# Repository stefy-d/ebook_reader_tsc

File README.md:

## **Manea Ștefania-Delia**
### **Grupa 335CC** 
<br><br>

# **Pașii de implementare**  
- Realizarea schematicului
- Plasarea componentelor pe PCB
- Trasarea circuitelor și optimizarea rutării semnalelor
- Încărcarea modelelor 3D pentru fiecare componentă
- Crearea bateriei și a display-ului
- Inserarea PCB-ului, a bateriei și a display-ului în carcasa 3D
<br><br> 

# **Diagramă bloc**
```` mermaid
graph TD;
    USB_C[USB C Connector & ESD Protection] -->|Power & Data| LDO[LDO Voltage Regulator];
    LDO -->|3.3V Power| ESP32[ESP32 C6];
    LDO -->|3.3V Power| SD[SD Card];
    LDO -->|3.3V Power| RTC[RTC Module DS3231SN];
    LDO -->|3.3V Power| Sensor[Environmental Sensor BME688];
    LDO -->|3.3V Power| Display[EPD Power];
    ESP32 -->|SPI| SD;
    ESP32 -->|I2C| RTC;
    ESP32 -->|I2C| Sensor;
    ESP32 -->|SPI| Display;
    ESP32 -->|GPIO| Button[Voltage Supervisor + Reset & Boot / IO Button];
    ESP32 -->|SPI| Flash[External NOR Flash 64MB];
    ESP32 -->|GPIO| ChargeLevel[Battery Charge Level];
    ESP32 -->|GPIO| Selector[Display Type Selector];
    ChargeController[Li-Po Battery Charging Controller] -->|Power| LDO;
    ChargeController -->|Battery Status| ChargeLevel;

`````
<br><br>

# **BOM (Bill Of Materials)**

| Componenta      | X      | Y      | Rotatie | Valoare | Package | Link | 
|----------------|--------|--------|----------|------------------------|----------------------------------------|-----------------------------------|  
| BOOT_BUTTON    | 23.90  | 108.41 | 180.00   | BUTTON_CUSYOMV1         | MYBUTTON | https://industry.panasonic.com/global/en/products/control/switch/light-touch/number/evqpuj02k |
| C1             | 154.64 | 6.13   | 90.00    | 100nF                  | ESP32_WROVER_EAGLE-LTSPICE_C0402       | https://componentsearchengine.com/part-view/CC0402MRX5R5BB106/YAGEO |
| C10            | 67.34  | 107.83 | 270.00   | 100nF                  | ESP32_WROVER_EAGLE-LTSPICE_C0402       | https://componentsearchengine.com/part-view/CC0402MRX5R5BB106/YAGEO |
| C10_SUPERCAP   | 93.09  | 55.34  | 90.00    | CPH3225A               | CAPCP3225X100N  | https://www.snapeda.com/parts/CPH3225A/Seiko+Instruments/view-part/?ref=eda |
| C1_BAT         | 107.73 | 50.25  | 0.00     | 4.7uF                  | ESP32_WROVER_EAGLE-LTSPICE_C0402       | https://componentsearchengine.com/part-view/CC0402MRX5R5BB106/YAGEO |
| C1_BAT1        | 109.19 | 37.99  | 0.00     | 4.7uF                  | ESP32_WROVER_EAGLE-LTSPICE_C0402       | https://componentsearchengine.com/part-view/CC0402MRX5R5BB106/YAGEO |
| C1_BAT2        | 104.58 | 40.47  | 90.00    | 4.7uF                  | ESP32_WROVER_EAGLE-LTSPICE_C0402       | https://componentsearchengine.com/part-view/CC0402MRX5R5BB106/YAGEO |
| C2             | 153.42 | 6.13   | 90.00    | 100nF                  | ESP32_WROVER_EAGLE-LTSPICE_C0402       | https://componentsearchengine.com/part-view/CC0402MRX5R5BB106/YAGEO |
| C2_BAT         | 120.94 | 51.25  | 90.00    | 4.7uF                  | ESP32_WROVER_EAGLE-LTSPICE_C0402       | https://componentsearchengine.com/part-view/CC0402MRX5R5BB106/YAGEO |
| C3             | 118.89 | 41.40  | 90.00    | 100uF                  | RCL_CT3528 | https://eu.mouser.com/ProductDetail/KYOCERA-AVX/F910J107MBAAJ6?qs=PqoDHHvF649LraCA%2FjeGXg%3D%3D |
| C4             | 90.95  | 35.19  | 90.00    | 4.7uF/25V              | ESP32_WROVER_EAGLE-LTSPICE_C0402       | https://componentsearchengine.com/part-view/CC0402MRX5R5BB106/YAGEO |
| C4_USB         | 149.29 | 50.17  | 90.00    | 100nF                  | ESP32_WROVER_EAGLE-LTSPICE_C0402       | https://componentsearchengine.com/part-view/CC0402MRX5R5BB106/YAGEO |
| C5             | 52.21  | 107.71 | 270.00   | 1uF                    | ESP32_WROVER_EAGLE-LTSPICE_C0402       | https://componentsearchengine.com/part-view/CC0402MRX5R5BB106/YAGEO |
| C5_USB         | 155.40 | 52.97  | 90.00    | 4.7uF                  | ESP32_WROVER_EAGLE-LTSPICE_C0402       | https://componentsearchengine.com/part-view/CC0402MRX5R5BB106/YAGEO |
| C6             | 27.30  | 107.83 | 270.00   | 100nF                  | ESP32_WROVER_EAGLE-LTSPICE_C0402       | https://componentsearchengine.com/part-view/CC0402MRX5R5BB106/YAGEO |
| C7             | 80.29  | 30.73  | 0.00     | 10uF                   | ESP32_WROVER_EAGLE-LTSPICE_C0402       | https://componentsearchengine.com/part-view/CC0402MRX5R5BB106/YAGEO |
| C8             | 84.28  | 52.43  | 180.00   | 100nF                  | ESP32_WROVER_EAGLE-LTSPICE_C0402       | https://componentsearchengine.com/part-view/CC0402MRX5R5BB106/YAGEO |
| C9             | 10.66  | 99.03  | 90.00    | 100nF                  | ESP32_WROVER_EAGLE-LTSPICE_C0402       | https://componentsearchengine.com/part-view/CC0402MRX5R5BB106/YAGEO |
| CHANGE_BUTTON  | 64.00  | 108.48 | 179.30   | BUTTON_CUSYOMV1         | MYBUTTON | https://industry.panasonic.com/global/en/products/control/switch/light-touch/number/evqpuj02k |
| CHG_LED        | 111.34 | 50.15  | 90.00    |                        | ADAFRUIT_CHIP-LED0603                  | https://www.snapeda.com/parts/KP-1608SURCK/Kingbright/view-part/?ref=search&t=LED%200603 |
| C_DELAY        | 51.93  | 101.29 | 269.50   | 100nF                  | ESP32_WROVER_EAGLE-LTSPICE_C0402       | https://componentsearchengine.com/part-view/CC0402MRX5R5BB106/YAGEO |
| D1             | 152.58 | 50.47  | 0.00     | USBLC6-2SC6Y            | SOT95P280X145-6N                       | https://www.snapeda.com/parts/USBLC6-2SC6Y/STMicroelectronics/view-part/?ref=eda |
| D10            | 44.62  | 38.77  | 90.00    | PGB1010603MR            | DIOC1608X36N                           | https://www.snapeda.com/parts/PGB1010603MR/Littelfuse/view-part/?ref=eda |
| D11            | 42.60  | 38.67  | 90.00    | PGB1010603MR            | DIOC1608X36N                           | https://www.snapeda.com/parts/PGB1010603MR/Littelfuse/view-part/?ref=eda |
| D12            | 38.38  | 38.87  | 90.00    | PGB1010603MR            | DIOC1608X36N                           | https://www.snapeda.com/parts/PGB1010603MR/Littelfuse/view-part/?ref=eda |
| D2             | 122.09 | 41.08  | 90.00    | ESP32_WROVER_AVX---SD0805S020S1R0_AVX_SD0805S020S1R0_0_0AVX_SD0805S020S1R0_0_0 | ESP32_WROVER_AVX---SD0805S020S1R0_AVX_SD0805S020S1R0_0 | https://eu.mouser.com/ProductDetail/KYOCERA-AVX/SD0805S020S1R0?qs=jCA%252BPfw4LHbpkAoSnwrdjw%3D%3D |
| D3             | 87.16  | 35.47  | 180.00   | MBR0530                 | SOD3716X135N                           | https://www.snapeda.com/parts/MBR0530/Onsemi/view-part/?ref=eda |
| D4             | 87.22  | 31.68  | 0.00     | MBR0530                 | SOD3716X135N                           | https://www.snapeda.com/parts/MBR0530/Onsemi/view-part/?ref=eda |
| D5             | 80.26  | 40.58  | 180.00   | MBR0530                 | SOD3716X135N                           | https://www.snapeda.com/parts/MBR0530/Onsemi/view-part/?ref=eda |
| D6             | 73.98  | 26.87  | 0.00     | PGB1010603MR            | DIOC1608X36N                           | https://www.snapeda.com/parts/PGB1010603MR/Littelfuse/view-part/?ref=eda |
| D7             | 83.64  | 68.93  | 0.00     | ESP32_WROVER_AVX---SD0805S020S1R0_AVX_SD0805S020S1R0_0_0AVX_SD0805S020S1R0_0_0 | ESP32_WROVER_AVX---SD0805S020S1R0_AVX_SD0805S020S1R0_0 | https://eu.mouser.com/ProductDetail/KYOCERA-AVX/SD0805S020S1R0?qs=jCA%252BPfw4LHbpkAoSnwrdjw%3D%3D |
| D8             | 14.96  | 98.57  | 0.00     | PGB1010603MR            | DIOC1608X36N                           | https://www.snapeda.com/parts/PGB1010603MR/Littelfuse/view-part/?ref=eda
| D9             | 33.14  | 47.17  | 270.00   | PGB1010603MR            | DIOC1608X36N                           | https://www.snapeda.com/parts/PGB1010603MR/Littelfuse/view-part/?ref=eda |
| EPD_C1         | 88.71  | 21.47  | 90.00    | 1uF/50V                | ESP32_WROVER_EAGLE-LTSPICE_C0402       | https://componentsearchengine.com/part-view/CC0402MRX5R5BB106/YAGEO |
| EPD_C10        | 76.31  | 21.47  | 90.00    | 1uF/50V                | ESP32_WROVER_EAGLE-LTSPICE_C0402       | https://componentsearchengine.com/part-view/CC0402MRX5R5BB106/YAGEO |
| EPD_C11        | 72.05  | 18.89  | 90.00    | 1uF/50V                | ESP32_WROVER_EAGLE-LTSPICE_C0402       | https://componentsearchengine.com/part-view/CC0402MRX5R5BB106/YAGEO |
| EPD_C12        | 70.61  | 18.79  | 90.00    | 1uF/50V                | ESP32_WROVER_EAGLE-LTSPICE_C0402       |   https://componentsearchengine.com/part-view/CC0402MRX5R5BB106/YAGEO |
| EPD_C2         | 87.32  | 21.47  | 90.00    | 1uF/50V                | ESP32_WROVER_EAGLE-LTSPICE_C0402       |   https://componentsearchengine.com/part-view/CC0402MRX5R5BB106/YAGEO |
| EPD_C5         | 85.68  | 21.45  | 90.00    | 1uF/50V                | ESP32_WROVER_EAGLE-LTSPICE_C0402       |   https://componentsearchengine.com/part-view/CC0402MRX5R5BB106/YAGEO |
| EPD_C6         | 81.95  | 21.49  | 270.00   | 1uF/50V                | ESP32_WROVER_EAGLE-LTSPICE_C0402       |   https://componentsearchengine.com/part-view/CC0402MRX5R5BB106/YAGEO |
| EPD_C7         | 80.55  | 21.50  | 90.00    | 1uF/50V                | ESP32_WROVER_EAGLE-LTSPICE_C0402       |   https://componentsearchengine.com/part-view/CC0402MRX5R5BB106/YAGEO |
| EPD_C8         | 79.15  | 21.51  | 90.00    | 1uF/50V                | ESP32_WROVER_EAGLE-LTSPICE_C0402       |   https://componentsearchengine.com/part-view/CC0402MRX5R5BB106/YAGEO |
| EPD_C9         | 77.75  | 21.52  | 90.00    | 1uF/50V                | ESP32_WROVER_EAGLE-LTSPICE_C0402       |   https://componentsearchengine.com/part-view/CC0402MRX5R5BB106/YAGEO |
| IC1            | 48.65  | 101.27 | 0.00     | BD5229G-TR             | SOT95P280X125-5N                       | https://componentsearchengine.com/part-view/BD5229G-TR/ROHM%20Semiconductor |
| IC4            | 113.73 | 40.29  | 0.00     | XC6220A331MR-G         | SOT95P280X120-5N | https://componentsearchengine.com/part-view/XC6220A331MR-G/Torex |
| J1        | 83.10  | 14.17  | 0.00     | FH34SRJ-24S-0.5SH_99_ | FH34SRJ24S05SH99                               | https://componentsearchengine.com/part-view/FH34SRJ-24S-0.5SH(99)/Hirose |
| J2        | 165.53 | 54.30  | 90.00    | SAMACSYS_PARTS_USB4110-GF-A | SAMACSYS_PARTS_USB4110GFA                     | https://componentsearchengine.com/part-view/USB4110-GF-A/GCT%20(GLOBAL%20CONNECTOR%20TECHNOLOGY) |
| J3        | 166.35 | 19.30  | 90.00    | QWIIC_RIGHT_ANGLE | JST04_1MM_RA                                  | https://eu.mouser.com/ProductDetail/Adafruit/4208?qs=PzGy0jfpSMtbScLbr0L5dw%3D%3D |
| J4        | 9.09   | 88.88  | 270.00   | 112A-TAAR-R03_ATTEND | 112ATAARR03ATTEND                             | https://store.comet.srl.ro/Catalogue/Product/43497/ |
| L1        | 80.35  | 35.77  | 270.00   | 68uH            | IND_4828-WE-TPC_WRE                           | https://eu.mouser.com/ProductDetail/Wurth-Elektronik/744043680?qs=PGXP4M47uW6VkZq%252BkzjrHA%3D%3D |
| MCP73831  | 116.79 | 49.69  | 90.00    | ESP32_WROVER_SPARKFUN-IC-POWER_MCP73831 | ESP32_WROVER_SPARKFUN-IC-POWER_SOT23-5 | https://eu.mouser.com/ProductDetail/Microchip-Technology/MCP73831T-2ACI-OT?qs=yUQqVecv4qvbBQBGbHx0Mw%3D%3D |
| PFMF.050.1| 151.74 | 43.60  | 0.00     | ESP32C6_VARISTORCN1812 | ESP32C6_VARISTOR_CT/CN1812                    | https://www.mouser.co.uk/ProductDetail/EPCOS-TDK/B72520T0350K062?qs=dEfas%2FXlABIszF52uu7vrg%3D%3D |
| Q1        | 123.56 | 47.31  | 0.00     | 20V/4.2A/52mΩ/1.4W | ESP32_WROVER_SPARKFUN-DISCRETESEMI_SOT23-3    | https://componentsearchengine.com/part-view/DMG2305UX-7/Diodes%20Incorporated |
| Q2        | 76.03  | 31.36  | 270.00   | 20V/4.2A/52mΩ/1.4W | ESP32_WROVER_SPARKFUN-DISCRETESEMI_SOT23-3    | https://componentsearchengine.com/part-view/DMG2305UX-7/Diodes%20Incorporated |
| Q3        | 67.19  | 15.28  | 90.00    | SI1308EDL-T1-GE3 | SOT65P210X110-3N                              | https://www.snapeda.com/parts/SI1308EDL-T1-GE3/Vishay+Siliconix/view-part/?ref=eda |
| R1        | 19.35  | 42.13  | 270.00   | 10K             | ESP32_WROVER_EAGLE-LTSPICE_R0402              | https://componentsearchengine.com/part-view/R0402%201%25%20100%20K%20(RC0402FR-07100KL)/YAGEO |
| R10       | 12.23  | 99.03  | 90.00    | 10K             | ESP32_WROVER_EAGLE-LTSPICE_R0402              | https://componentsearchengine.com/part-view/R0402%201%25%20100%20K%20(RC0402FR-07100KL)/YAGEO |
| R1_BAT    | 111.55 | 48.75  | 0.00     | 200             | ESP32_WROVER_EAGLE-LTSPICE_R0402              |
| R1_PINH   | 156.12 | 6.27   | 90.00    | 10K             | ESP32_WROVER_EAGLE-LTSPICE_R0402              | https://componentsearchengine.com/part-view/R0402%201%25%20100%20K%20(RC0402FR-07100KL)/YAGEO |
| R1_PINH1  | 83.56  | 66.94  | 0.00     | 10K             | ESP32_WROVER_EAGLE-LTSPICE_R0402              | https://componentsearchengine.com/part-view/R0402%201%25%20100%20K%20(RC0402FR-07100KL)/YAGEO |
| R1_PWRUSB | 106.25 | 40.54  | 90.00    | 100k            | ESP32_WROVER_EAGLE-LTSPICE_R0402              | https://componentsearchengine.com/part-view/R0402%201%25%20100%20K%20(RC0402FR-07100KL)/YAGEO |
| R2        | 65.73  | 11.51  | 0.00     | 2.2             | ESP32_WROVER_EAGLE-LTSPICE_R0402              | https://componentsearchengine.com/part-view/R0402%201%25%20100%20K%20(RC0402FR-07100KL)/YAGEO |
| R2-PINH   | 157.48 | 6.27   | 90.00    | 10K             | ESP32_WROVER_EAGLE-LTSPICE_R0402              | https://componentsearchengine.com/part-view/R0402%201%25%20100%20K%20(RC0402FR-07100KL)/YAGEO |
| R2-USB    | 152.58 | 46.33  | 0.00     | 5k1             | ESP32_WROVER_EAGLE-LTSPICE_R0402              | https://componentsearchengine.com/part-view/R0402%201%25%20100%20K%20(RC0402FR-07100KL)/YAGEO |
| R2-USB1   | 152.56 | 47.77  | 0.00     | 5k1             | ESP32_WROVER_EAGLE-LTSPICE_R0402              | https://componentsearchengine.com/part-view/R0402%201%25%20100%20K%20(RC0402FR-07100KL)/YAGEO |
| R2_BAT    | 115.66 | 46.05  | 90.00    | 2K              | ESP32_WROVER_EAGLE-LTSPICE_R0402              | https://componentsearchengine.com/part-view/R0402%201%25%20100%20K%20(RC0402FR-07100KL)/YAGEO |
| R2_PINH1  | 89.11  | 63.79  | 90.00    | 10K             | ESP32_WROVER_EAGLE-LTSPICE_R0402              | https://componentsearchengine.com/part-view/R0402%201%25%20100%20K%20(RC0402FR-07100KL)/YAGEO |
| R3        | 68.71  | 9.53   | 90.00    | 0.47            | ESP32_WROVER_EAGLE-LTSPICE_R0402              | https://componentsearchengine.com/part-view/R0402%201%25%20100%20K%20(RC0402FR-07100KL)/YAGEO |
| R4        | 70.49  | 13.91  | 0.00     | 10K             | ESP32_WROVER_EAGLE-LTSPICE_R0402              | https://componentsearchengine.com/part-view/R0402%201%25%20100%20K%20(RC0402FR-07100KL)/YAGEO |
| R5        | 31.21  | 47.21  | 270.00   | 10K             | ESP32_WROVER_EAGLE-LTSPICE_R0402              | https://componentsearchengine.com/part-view/R0402%201%25%20100%20K%20(RC0402FR-07100KL)/YAGEO |
| R6        | 44.53  | 33.41  | 92.20    | 10K             | ESP32_WROVER_EAGLE-LTSPICE_R0402              | https://componentsearchengine.com/part-view/R0402%201%25%20100%20K%20(RC0402FR-07100KL)/YAGEO |
| R7        | 42.45  | 33.61  | 270.00   | 10K             | ESP32_WROVER_EAGLE-LTSPICE_R0402              | https://componentsearchengine.com/part-view/R0402%201%25%20100%20K%20(RC0402FR-07100KL)/YAGEO |
| R8        | 38.57  | 33.41  | 90.00    | 10K             | ESP32_WROVER_EAGLE-LTSPICE_R0402              | https://componentsearchengine.com/part-view/R0402%201%25%20100%20K%20(RC0402FR-07100KL)/YAGEO |
| R9        | 70.89  | 31.31  | 90.00    | 10K             | ESP32_WROVER_EAGLE-LTSPICE_R0402              | https://componentsearchengine.com/part-view/R0402%201%25%20100%20K%20(RC0402FR-07100KL)/YAGEO |
| RESET_BUTTON | 48.90 | 108.49 | 180.40 | BUTTON_CUSYOMV1  | MYBUTTON | https://industry.panasonic.com/global/en/products/control/switch/light-touch/number/evqpuj02k |
| R_BOOT    | 20.27  | 107.67  | 270.00   | 10K             | ESP32_WROVER_EAGLE-LTSPICE_R0402              | https://componentsearchengine.com/part-view/R0402%201%25%20100%20K%20(RC0402FR-07100KL)/YAGEO |
| R_CAPACITOR | 88.95 | 55.04  | 270.00   | 15              | ESP32_WROVER_EAGLE-LTSPICE_R0402              | https://componentsearchengine.com/part-view/R0402%201%25%20100%20K%20(RC0402FR-07100KL)/YAGEO |
| R_CHANGE  | 60.62  | 107.78  | 90.00    | 10K             | ESP32_WROVER_EAGLE-LTSPICE_R0402              | https://componentsearchengine.com/part-view/R0402%201%25%20100%20K%20(RC0402FR-07100KL)/YAGEO |
| R_CL1     | 72.96  | 31.23  | 90.00    | 10K             | ESP32_WROVER_EAGLE-LTSPICE_R0402              | https://componentsearchengine.com/part-view/R0402%201%25%20100%20K%20(RC0402FR-07100KL)/YAGEO |
| R_RESET   | 45.19  | 107.69  | 269.80   | 10K             | ESP32_WROVER_EAGLE-LTSPICE_R0402              | https://componentsearchengine.com/part-view/R0402%201%25%20100%20K%20(RC0402FR-07100KL)/YAGEO |
| SENSOR2   | 154.46 | 10.42  | 90.00    | ESP32_WROVER_BME680_BME680 | ESP32_WROVER_BME680_PSON80P300X300X100-8N | https://www.snapeda.com/parts/BME680/Bosch/view-part/?welcome=home |
| SJ1       | 65.86  | 9.29   | 0.00     |                 | SJ                                            | https://grabcad.com/library/solder-jumpers-1 |
| TP1       | 10.51  | 67.29  | 0.00     | TPTP20R         | TP20R                                          | CUSTOM
| TP10      | 104.28 | 15.51  | 0.00     | TPTP20R         | TP20R                                          | CUSTOM
| TP11      | 100.19 | 19.39  | 0.00     | TPTP20R         | TP20R                                          | CUSTOM
| TP12      | 99.83  | 15.81  | 0.00     | TPTP20R         | TP20R                                          | CUSTOM
| TP13      | 94.86  | 15.83  | 0.00     | TPTP20R         | TP20R                                          | CUSTOM
| TP14      | 135.63 | 50.31  | 0.00     | TPTP20R         | TP20R                                          | CUSTOM
| TP15      | 78.68  | 70.51  | 0.00     | TPTP20R         | TP20R                                          | CUSTOM
| TP16      | 9.43   | 41.31  | 0.00     | TPTP20R         | TP20R                                          | CUSTOM
| TP17      | 95.62  | 19.47  | 0.00     | TPTP20R         | TP20R                                          | CUSTOM
| TP2       | 14.23  | 67.49  | 0.00     | TPTP20R         | TP20R                                          | CUSTOM
| TP3       | 131.25 | 50.56  | 0.00     | TPTP20R         | TP20R                                          | CUSTOM
| TP4       | 131.37 | 54.49  | 0.00     | TPTP20R         | TP20R                                          | CUSTOM
| TP5       | 135.89 | 54.39  | 0.00     | TPTP20R         | TP20R                                          | CUSTOM
| TP6       | 16.11  | 77.59  | 0.00     | TPTP20R         | TP20R                                          | CUSTOM
| TP7       | 11.03  | 77.59  | 0.00     | TPTP20R         | TP20R                                          | CUSTOM
| TP8       | 5.95   | 77.59  | 0.00     | TPTP20R         | TP20R                                          | CUSTOM
| TP9       | 104.67 | 19.19  | 0.00     | TPTP20R         | TP20R                                          | CUSTOM
| U1        | 36.89  | 54.16  | 0.00     | W25Q512JVEIQ    | SON127P600X800X80-9N                           | https://www.snapeda.com/parts/W25Q512JVEIQ/Winbond+Electronics/view-part/?ref=eda |
| U2        | 16.20  | 54.00  | 90.00    | ESP32-C6-WROOM-1-N8 | XCVR_ESP32-C6-WROOM-1-N8                     | https://www.snapeda.com/parts/ESP32-C6-WROOM-1-N8/Espressif+Systems/view-part/?ref=eda |
| U3        | 79.90  | 59.90  | 270.00   | DS3231SN#       | SOIC127P1032X265-16N                           | https://www.snapeda.com/parts/DS3231SN%23/Analog+Devices/view-part/?ref=eda |
| U4        | 126.58 | 50.72  | 0.00     | MAX17048G+T10   | SON50P200X200X80-9N                            | https://www.snapeda.com/parts/MAX17048G+T10/Analog+Devices/view-part/?ref=eda |

<br><br>

# **Pini ESP32-C6**

ESP32-C6 are mai mulți pini utilizați pentru conectarea componentelor din schema bloc. Mai jos este o descriere detaliată a pinilor folosiți și justificarea utilizării lor:

### **1. SD Card (SPI)**
   - **Pini utilizați**:
     - **IO6 (CLK/SCK)** - Semnal de ceas SPI
     - **IO7 (MOSI)** - Linie de date pentru transmitere
     - **IO2 (MISO)** - Linie de date pentru recepție
     - **IO10 (CS)** - Chip Select pentru activarea cardului SD
   - **Motiv**: Protocolul SPI este ideal pentru cardurile SD, deoarece permite viteze mari de transfer cu un număr redus de pini.

### **2. RTC Module DS3231SN (I2C)**
   - **Pini utilizați**:
     - **IO8 (SCL)** - Linie de ceas I2C
     - **IO9 (SDA)** - Linie de date I2C
   - **Motiv**: DS3231SN folosește protocolul I2C pentru comunicație, ceea ce permite partajarea magistralei cu alți senzori.

### **3. Environmental Sensor BME688 (I2C)**
   - **Pini utilizați**:
     - **IO8 (SCL)** - Linie de ceas I2C (partajat cu RTC)
     - **IO9 (SDA)** - Linie de date I2C (partajat cu RTC)
   - **Motiv**: Folosind I2C, senzorul poate comunica eficient cu ESP32 fără a ocupa pini suplimentari.

### **4. EPD Power (SPI)**
   - **Pini utilizați**:
     - **IO6 (CLK/SCK)** - Semnal de ceas SPI
     - **IO7 (MOSI)** - Linie de date pentru transmitere
     - **IO2 (MISO)** - Linie de date pentru recepție
     - **IO5 (CS)** - Chip Select pentru activarea display-ului
   - **Motiv**: Ecranele E-Paper folosesc adesea SPI datorită vitezei mari de transmitere și latenței reduse.

### **5. Voltage Supervisor + Reset & Boot / IO Button (GPIO)**
   - **Pini utilizați**:
     - **IO0** - Buton BOOT
     - **IO3** - Buton Reset
   - **Motiv**: ESP32 folosește aceste pini pentru a intra în mod de programare și resetare rapidă.

### **6. External NOR Flash 64MB (SPI)**
   - **Pini utilizați**:
     - **IO6 (CLK/SCK)** - Semnal de ceas SPI
     - **IO7 (MOSI)** - Linie de date pentru transmitere
     - **IO2 (MISO)** - Linie de date pentru recepție
     - **IO4 (CS)** - Chip Select pentru activarea memoriei Flash
   - **Motiv**: ESP32 poate extinde memoria utilizând SPI pentru a accesa rapid datele stocate.

### **7. Battery Charge Level (GPIO)**
   - **Pini utilizați**:
     - **IO12 (ADC1_CH3)** - Intrare analogică pentru măsurarea tensiunii bateriei
   - **Motiv**: ESP32 dispune de convertoare ADC care permit măsurarea nivelului de încărcare al bateriei.

### **8. Display Type Selector (GPIO)**
   - **Pini utilizați**:
     - **IO14** - Selector de tip ecran (ex. alb-negru vs. color)
   - **Motiv**: Un pin GPIO poate fi folosit pentru a configura sau selecta diferite moduri de operare ale ecranului.

<br><br>

# **Descriere hardware**  

## **1. Microcontrolerul principal – ESP32-C6**  

ESP32-C6 gestionează toate componentele conectate prin diverse protocoale de comunicație, asigurând interfațarea eficientă cu acestea.  

---

## **2. Module și senzori conectați la ESP32-C6: ca mai sus**  

### **2.1. Stocare – Card SD**  
- **Interfață de comunicare**: SPI   

---

### **2.2. Modul RTC DS3231SN**  
- **Interfață de comunicare**: I2C   

---

### **2.3. Senzor BME688** 
- **Interfață de comunicare**: I2C  

---

### **2.4. Ecran E-Paper (SPI)**  
- **Interfață de comunicare**: SPI 

---

### **2.5. Memorie externă NOR Flash 64MB**  
- **Interfață de comunicare**: SPI   

---

### **2.6. Butoane pentru control**   
- **Interfață de comunicare**: GPIO    

---

### **2.7. Monitorizare baterie**  
- **Interfață de comunicare**: GPIO / ADC  

---

### **2.8. Selector de tip ecran**   
- **Interfață de comunicare**: GPIO  

---

### **3. Alimentare și managementul energiei**  

ESP32-C6 și toate componentele funcționează la **3.3V**, alimentarea fiind gestionată de:  

1. **Regulator de tensiune LDO**   

2. **Controler de încărcare baterie Li-Po**  

---

### **4. Rezumat**  

| **Componentă**                        | **Interfață** | **Pini ESP32-C6**      |
|---------------------------------------|--------------|------------------------|
| **Card SD**                           | SPI          | IO6, IO7, IO2, IO10    |
| **RTC DS3231SN**                      | I2C          | IO8, IO9               |
| **Senzor BME688**                     | I2C          | IO8, IO9               |
| **Display E-Paper**                   | SPI          | IO6, IO7, IO2, IO5     |
| **Memorie NOR Flash 64MB**            | SPI          | IO6, IO7, IO2, IO4     |
| **Butoane de control**                | GPIO         | IO0, IO3               |
| **Monitorizare baterie**              | ADC/GPIO     | IO12                   |
| **Selector de tip ecran**             | GPIO         | IO14                   |

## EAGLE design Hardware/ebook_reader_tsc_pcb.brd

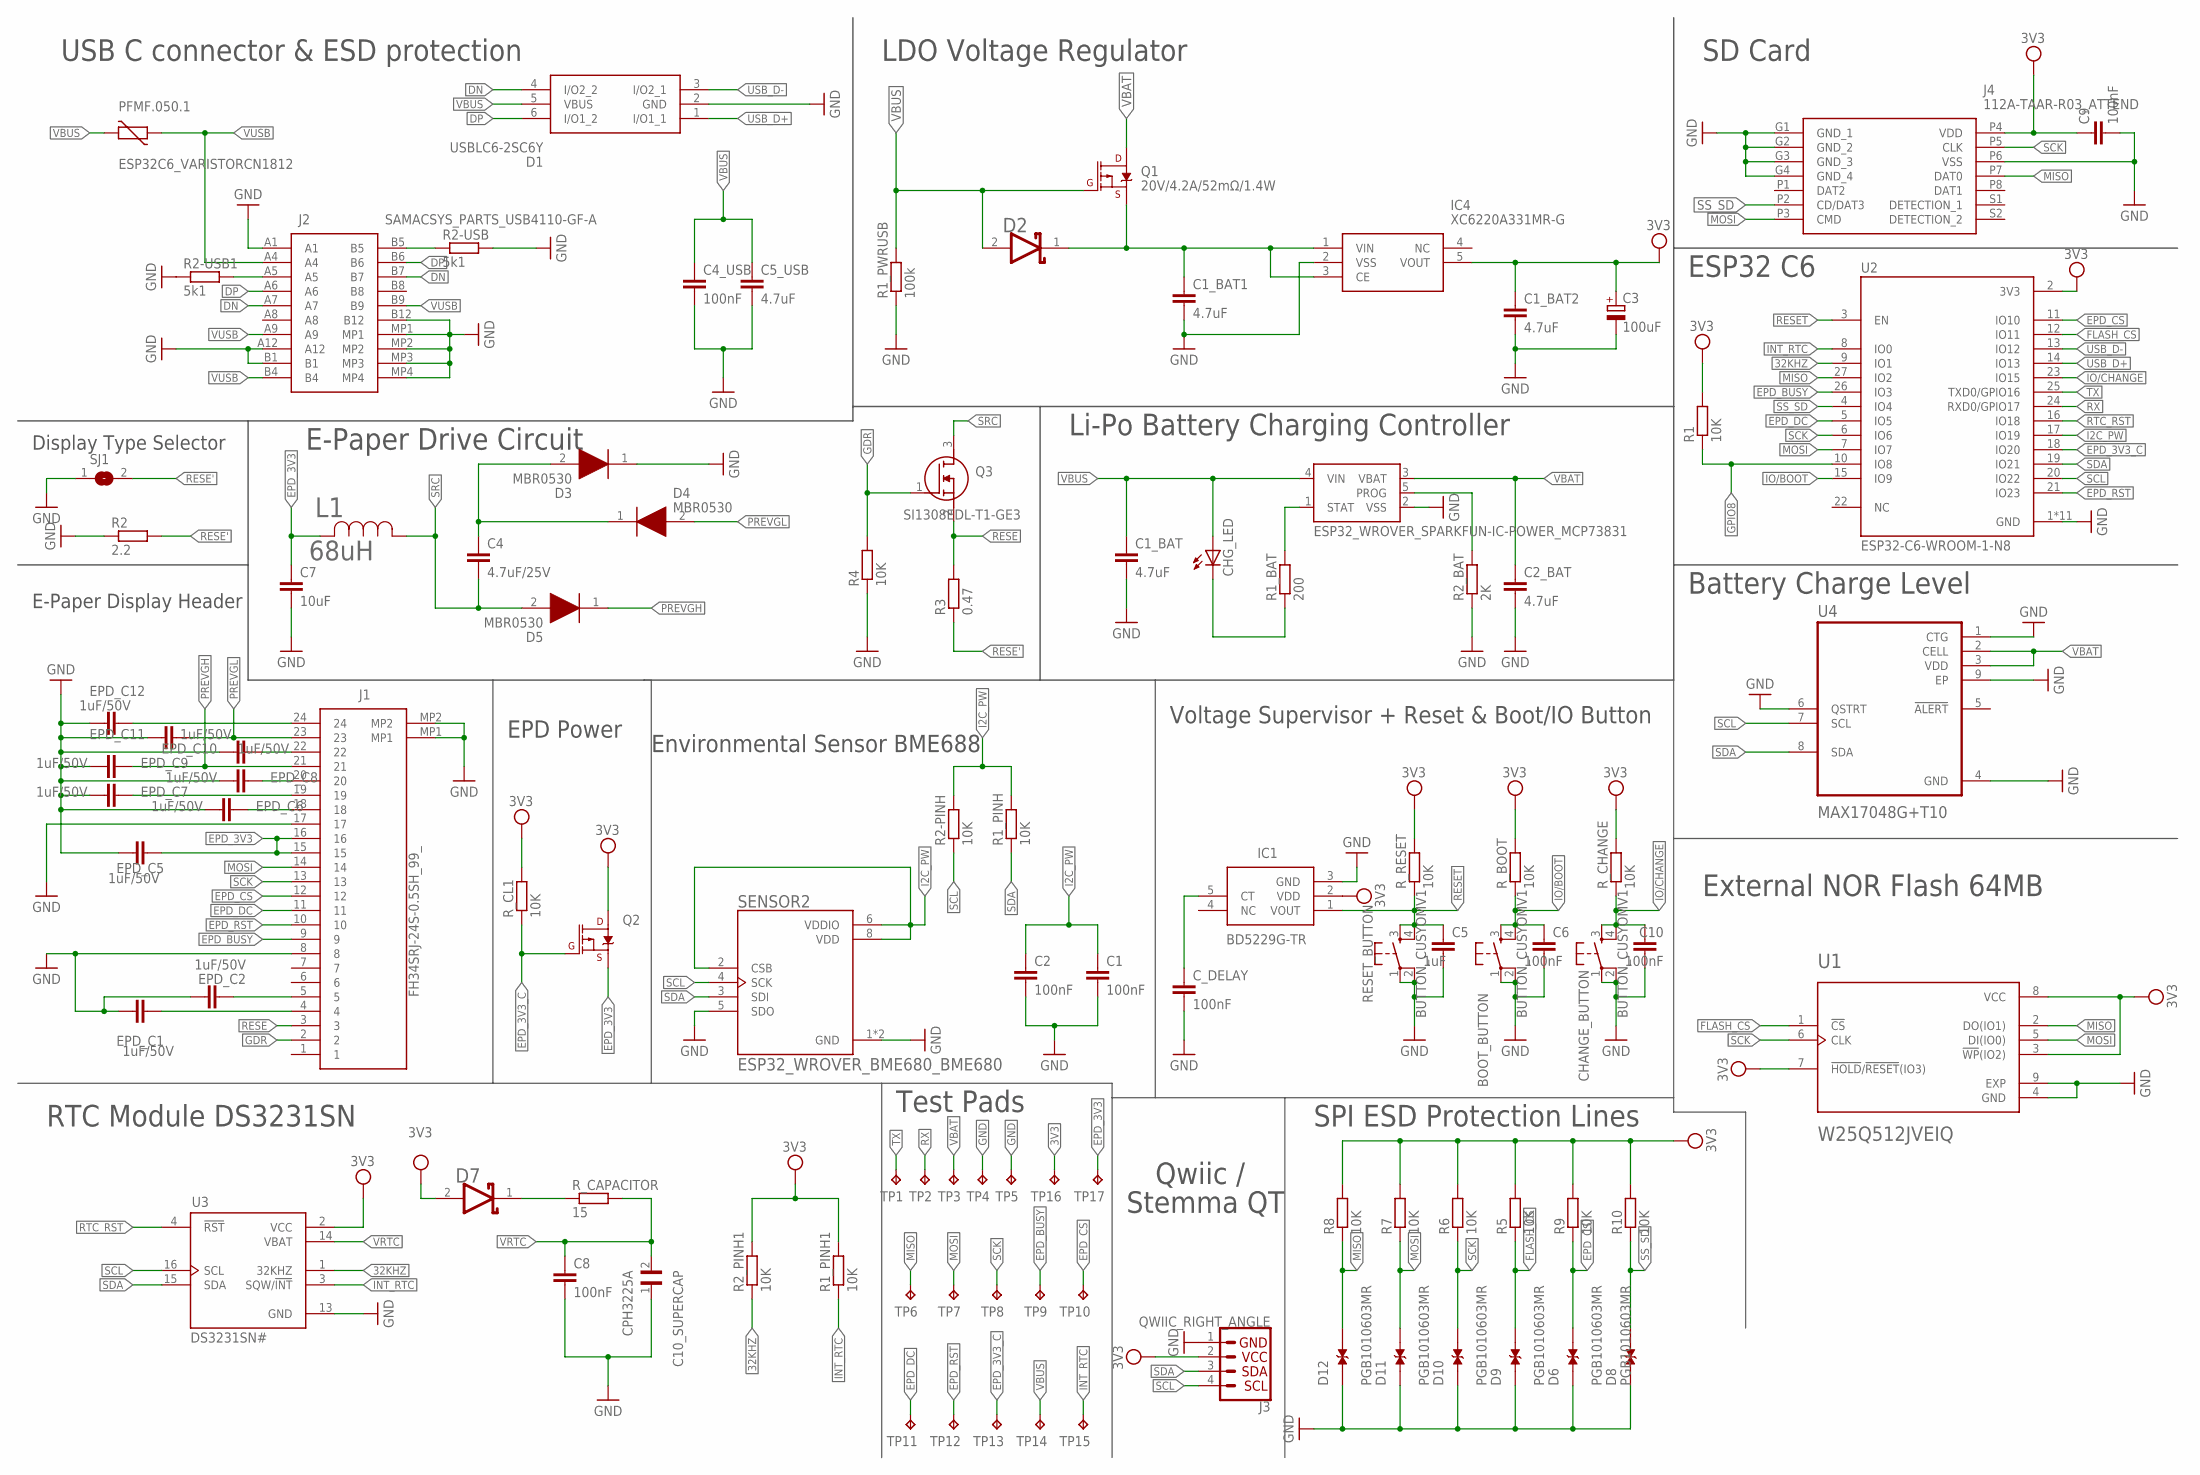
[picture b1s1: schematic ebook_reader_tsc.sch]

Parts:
BOOT_BUTTON: BUTTON_CUSYOMV1; MYBUTTON
C1, C2, C4_USB, C6, C8, C9, C10: 100nF; ESP32_WROVER_EAGLE-LTSPICE_C0402
C1_BAT, C1_BAT1, C1_BAT2, C2_BAT, C5_USB: 4.7uF; ESP32_WROVER_EAGLE-LTSPICE_C0402
C3: 100uF; RCL_CT3528
C4: 4.7uF/25V; ESP32_WROVER_EAGLE-LTSPICE_C0402
C5: 1uF; ESP32_WROVER_EAGLE-LTSPICE_C0402
C7: 10uF; ESP32_WROVER_EAGLE-LTSPICE_C0402
C10_SUPERCAP: CPH3225A; CAPCP3225X100N
CHANGE_BUTTON: BUTTON_CUSYOMV1; MYBUTTON
CHG_LED: ADAFRUIT_LEDCHIP-LED0603; ADAFRUIT_CHIP-LED0603
C_DELAY: 100nF; ESP32_WROVER_EAGLE-LTSPICE_C0402
D1: USBLC6-2SC6Y; SOT95P280X145-6N
D2, D7: ESP32_WROVER_AVX---SD0805S020S1R0_AVX_SD0805S020S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; ESP32_WROVER_AVX---SD0805S020S1R0_AVX_SD0805S020S1R0_0
D3, D4, D5: MBR0530; SOD3716X135N
D6, D8, D9, D10, D11, D12: PGB1010603MR; DIOC1608X36N
EPD_C1, EPD_C2, EPD_C5, EPD_C6, EPD_C7, EPD_C8, EPD_C9, EPD_C10, EPD_C11, EPD_C12: 1uF/50V; ESP32_WROVER_EAGLE-LTSPICE_C0402
IC1: BD5229G-TR; SOT95P280X125-5N
IC4: XC6220A331MR-G; SOT95P280X120-5N
J1: FH34SRJ-24S-0.5SH_99_; FH34SRJ24S05SH99
J2: SAMACSYS_PARTS_USB4110-GF-A; SAMACSYS_PARTS_USB4110GFA
J3: QWIIC_RIGHT_ANGLE; JST04_1MM_RA
J4: 112A-TAAR-R03_ATTEND; 112ATAARR03ATTEND
L1: 68uH; IND_4828-WE-TPC_WRE
MCP73831: ESP32_WROVER_SPARKFUN-IC-POWER_MCP73831; ESP32_WROVER_SPARKFUN-IC-POWER_SOT23-5
PFMF.050.1: ESP32C6_VARISTORCN1812; ESP32C6_VARISTOR_CT/CN1812
Q1, Q2: 20V/4.2A/52mΩ/1.4W; ESP32_WROVER_SPARKFUN-DISCRETESEMI_SOT23-3
Q3: SI1308EDL-T1-GE3; SOT65P210X110-3N
R1, R1_PINH, R1_PINH1, R2-PINH, R2_PINH1, R4, R5, R6, R7, R8, R9, R10: 10K; ESP32_WROVER_EAGLE-LTSPICE_R0402
R1_BAT: 200; ESP32_WROVER_EAGLE-LTSPICE_R0402
R1_PWRUSB: 100k; ESP32_WROVER_EAGLE-LTSPICE_R0402
R2: 2.2; ESP32_WROVER_EAGLE-LTSPICE_R0402
R2-USB, R2-USB1: 5k1; ESP32_WROVER_EAGLE-LTSPICE_R0402
R2_BAT: 2K; ESP32_WROVER_EAGLE-LTSPICE_R0402
R3: 0.47; ESP32_WROVER_EAGLE-LTSPICE_R0402
RESET_BUTTON: BUTTON_CUSYOMV1; MYBUTTON
R_BOOT: 10K; ESP32_WROVER_EAGLE-LTSPICE_R0402
R_CAPACITOR: 15; ESP32_WROVER_EAGLE-LTSPICE_R0402
R_CHANGE: 10K; ESP32_WROVER_EAGLE-LTSPICE_R0402
R_CL1: 10K; ESP32_WROVER_EAGLE-LTSPICE_R0402
R_RESET: 10K; ESP32_WROVER_EAGLE-LTSPICE_R0402
SENSOR2: ESP32_WROVER_BME680_BME680; ESP32_WROVER_BME680_PSON80P300X300X100-8N
SJ1: SJ
TP1, TP2, TP3, TP4, TP5, TP6, TP7, TP8, TP9, TP10, TP11, TP12, TP13, TP14, TP15, TP16, TP17: TPTP20R; TP20R
U1: W25Q512JVEIQ; SON127P600X800X80-9N
U2: ESP32-C6-WROOM-1-N8; XCVR_ESP32-C6-WROOM-1-N8
U3: DS3231SN#; SOIC127P1032X265-16N
U4: MAX17048G+T10; SON50P200X200X80-9N

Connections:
3V3: C1_BAT2.1, C3.+, C9.1, D7.2 (ANODE), IC1.2 (VDD), IC4.5 (VOUT), J3.2, J4.P4 (VDD), Q2.3 (D), R1.2, R1_PINH1.2, R2_PINH1.2, R5.2, R6.2, R7.2, R8.2, R9.2, R10.2, R_BOOT.2, R_CHANGE.2, R_CL1.2, R_RESET.2, TP16.TP, U1.3 (!WP!(IO2)), U1.7 (!HOLD!/!RESET!(IO3)), U1.8 (VCC), U2.2 (3V3), U3.2 (VCC)
32KHZ: R2_PINH1.1, U2.9 (IO1), U3.1 (32KHZ)
DN: D1.4 (I/O2_2), J2.A7, J2.B7
DP: D1.6 (I/O1_2), J2.A6, J2.B6
EPD_3V3: C7.1, EPD_C5.2, J1.15, J1.16, L1.2, Q2.2 (S), TP17.TP
EPD_3V3_C: Q2.1 (G), R_CL1.1, TP13.TP, U2.18 (IO20)
EPD_BUSY: J1.9, TP9.TP, U2.26 (IO3)
EPD_CS: D6.2, J1.12, R9.1, TP10.TP, U2.11 (IO10)
EPD_DC: J1.11, TP11.TP, U2.5 (IO5)
EPD_RST: J1.10, TP12.TP, U2.21 (IO23)
FLASH_CS: D9.2, R5.1, U1.1 (!CS), U2.12 (IO11)
GDR: J1.2, Q3.1 (G), R4.2
GND: BOOT_BUTTON.1, BOOT_BUTTON.2, C1.2, C1_BAT.2, C1_BAT1.2, C1_BAT2.2, C2.2, C2_BAT.2, C3.-, C4_USB.2, C5.2, C5_USB.2, C6.2, C7.2, C8.2, C10.2, C10_SUPERCAP.1, CHANGE_BUTTON.1, CHANGE_BUTTON.2, C_DELAY.2, D1.2 (GND), D3.1 (K), D6.1, D8.1, D9.1, D10.1, D11.1, D12.1, EPD_C1.1, EPD_C2.1, EPD_C5.1, EPD_C6.1, EPD_C7.1, EPD_C8.1, EPD_C9.1, EPD_C10.1, EPD_C11.1, EPD_C12.1, IC1.3 (GND), IC4.2 (VSS), J1.8, J1.17, J1.MP1, J1.MP2, J2.A12, J2.B1, J2.B12, J2.MP1, J2.MP2, J2.MP3, J2.MP4, J3.1, J4.G1 (GND_1), J4.G2 (GND_2), J4.G3 (GND_3), J4.G4 (GND_4), MCP73831.2 (VSS), R1_PWRUSB.1, R2.1, R2-USB.2, R2-USB1.1, R2_BAT.1, R4.1, RESET_BUTTON.1, RESET_BUTTON.2, SENSOR2.1 (GND), SENSOR2.5 (SDO), SENSOR2.7 (GND), SJ1.1, TP4.TP, TP5.TP, U1.4 (GND), U1.9 (EXP), U2.1 (GND), U2.28 (GND), U2.29_1 (GND), U2.29_2 (GND), U2.29_3 (GND), U2.29_4 (GND), U2.29_5 (GND), U2.29_6 (GND), U2.29_7 (GND), U2.29_8 (GND), U2.29_9 (GND), U3.13 (GND), U4.1 (CTG), U4.4 (GND), U4.6 (QSTRT), U4.9 (EP)
GPIO8: R1.1, U2.10 (IO8)
I2C_PW: C1.1, C2.1, R1_PINH.2, R2-PINH.2, SENSOR2.2 (CSB), SENSOR2.6 (VDDIO), SENSOR2.8 (VDD), U2.17 (IO19)
INT_RTC: R1_PINH1.1, TP15.TP, U2.8 (IO0), U3.3 (SQW/!INT)
IO/BOOT: BOOT_BUTTON.3, BOOT_BUTTON.4, C6.1, R_BOOT.1, U2.15 (IO9)
IO/CHANGE: C10.1, CHANGE_BUTTON.3, CHANGE_BUTTON.4, R_CHANGE.1, U2.23 (IO15)
MISO: D12.2, J4.P7 (DAT0), R8.1, TP6.TP, U1.2 (DO(IO1)), U2.27 (IO2)
MOSI: D11.2, J1.14, J4.P3 (CMD), R7.1, TP7.TP, U1.5 (DI(IO0)), U2.7 (IO7)
unnamed: J2.A5, R2-USB1.2
unnamed: J2.B5, R2-USB.1
unnamed: MCP73831.5 (PROG), R2_BAT.2
unnamed: C1_BAT1.1, D2.1 (CATHODE), IC4.1 (VIN), IC4.3 (CE), Q1.2 (S)
unnamed: C9.2, J4.P6 (VSS)
unnamed: CHG_LED.C, R1_BAT.1
unnamed: C4.1, D3.2 (A), D4.1 (K)
unnamed: MCP73831.1 (STAT), R1_BAT.2
unnamed: EPD_C1.2, J1.4
unnamed: C_DELAY.1, IC1.5 (CT)
unnamed: D7.1 (CATHODE), R_CAPACITOR.1
unnamed: EPD_C2.2, J1.5
unnamed: EPD_C12.2, J1.24
unnamed: EPD_C10.2, J1.22
unnamed: EPD_C8.2, J1.20
unnamed: EPD_C7.2, J1.19
unnamed: EPD_C6.2, J1.18
PREVGH: D5.1 (K), EPD_C9.2, J1.21
PREVGL: D4.2 (A), EPD_C11.2, J1.23
RESE: J1.3, Q3.2 (S), R3.2
RESE': R2.2, R3.1, SJ1.2
RESET: C5.1, IC1.1 (VOUT), RESET_BUTTON.3, RESET_BUTTON.4, R_RESET.1, U2.3 (EN)
RTC_RST: U2.16 (IO18), U3.4 (!RST)
RX: TP2.TP, U2.24 (RXD0/GPIO17)
SCK: D10.2, J1.13, J4.P5 (CLK), R6.1, TP8.TP, U1.6 (CLK), U2.6 (IO6)
SCL: J3.4, R2-PINH.1, SENSOR2.4 (SCK), U2.20 (IO22), U3.16 (SCL), U4.7 (SCL)
SDA: J3.3, R1_PINH.1, SENSOR2.3 (SDI), U2.19 (IO21), U3.15 (SDA), U4.8 (SDA)
SRC: C4.2, D5.2 (A), L1.1, Q3.3 (D)
SS_SD: D8.2, J4.P2 (CD/DAT3), R10.1, U2.4 (IO4)
TX: TP1.TP, U2.25 (TXD0/GPIO16)
USB_D+: D1.1 (I/O1_1), U2.14 (IO13)
USB_D-: D1.3 (I/O2_1), U2.13 (IO12)
VBAT: C2_BAT.1, MCP73831.3 (VBAT), Q1.3 (D), TP3.TP, U4.2 (CELL), U4.3 (VDD)
VBUS: C1_BAT.1, C4_USB.1, C5_USB.1, CHG_LED.A, D1.5 (VBUS), D2.2 (ANODE), MCP73831.4 (VIN), PFMF.050.1.2, Q1.1 (G), R1_PWRUSB.2, TP14.TP
VRTC: C8.1, C10_SUPERCAP.2, R_CAPACITOR.2, U3.14 (VBAT)
VUSB: J2.A4, J2.A9, J2.B4, J2.B9, PFMF.050.1.1

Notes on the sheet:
USB C connector & ESD protection
LDO Voltage Regulator
SD Card
ESP32 C6
Display Type Selector
Li-Po Battery Charging Controller
E-Paper Drive Circuit
Battery Charge Level
External NOR Flash 64MB
SPI ESD Protection Lines
Voltage Supervisor + Reset & Boot/IO Button
Qwiic /
Stemma QT
Test Pads
RTC Module DS3231SN
Environmental Sensor BME688
EPD Power
E-Paper Display Header

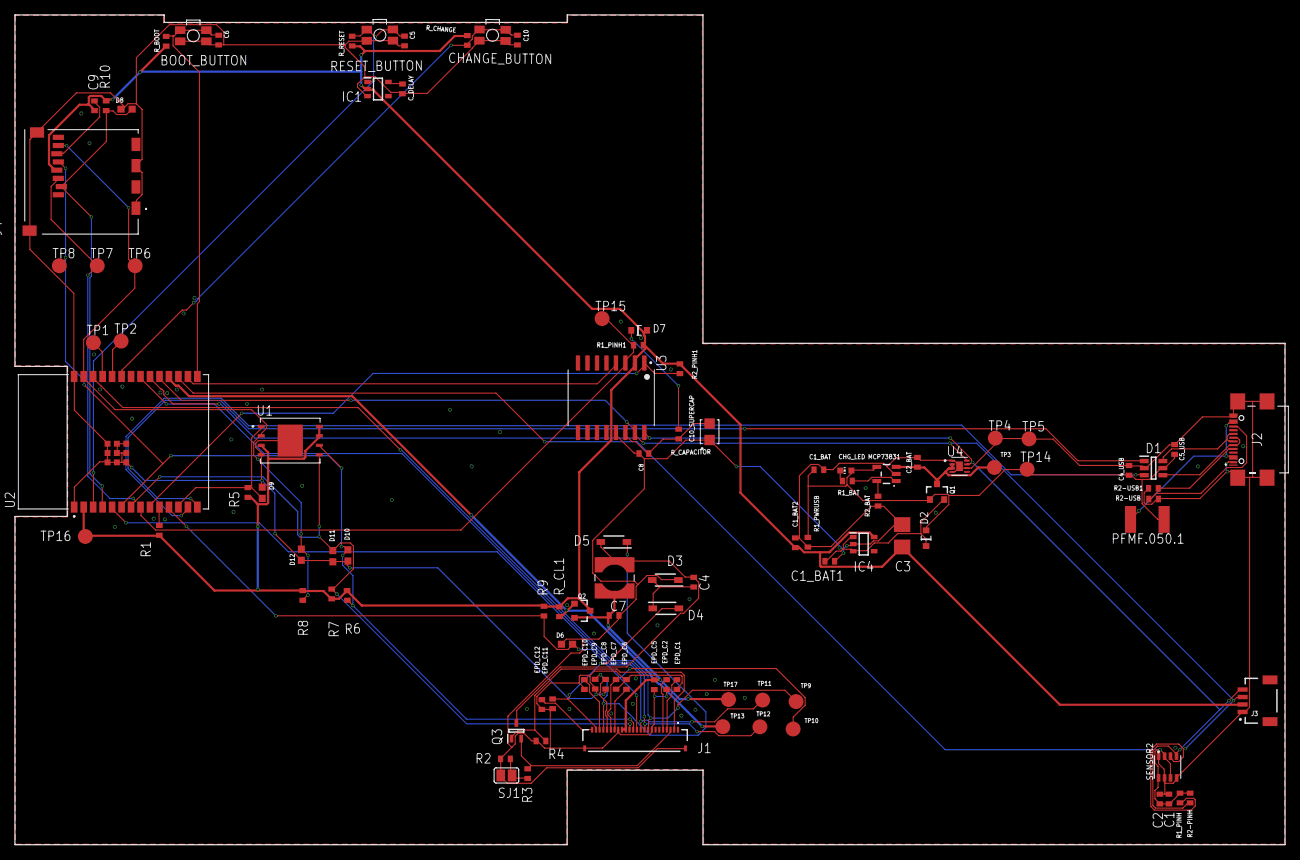
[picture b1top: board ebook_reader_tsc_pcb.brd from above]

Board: 2 copper layers, 170.2 x 111.2 mm, 103 parts (0 on the bottom side), 56 nets.

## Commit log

2025-04-02 Create LICENSE
2025-04-02 Create folder
2025-04-02 Create images
2025-04-02 Create 3d
2025-04-02 Create files
2025-04-02 Manufacturing
2025-04-02 files
2025-04-02 am pus zip pt ca era prea mare 3d-ul
2025-04-03 3dfinal
2025-04-13 updated pcb
    solved via stitching and overlapping layer names
2025-04-13 updated 3d
    3d pcb after modifying 2d pcb

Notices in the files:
parts and their libraries:
DeskAssistant v19 v1: COPYRIGHT: Copyright (C) 2024 Ultra Librarian. All rights reserved.
